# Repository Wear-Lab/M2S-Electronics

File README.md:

# M2S-Electronics
Electronics for the M2S Armband

## Details

This are the EAGLE files used to manufacture the four channel amplifier board
for the M2S Armband.

## JLCPCB manufacturing files

Files used to manufacture the PCB, including Gerber files, BOM, and PnP are
located in the JLCPCB folder.

## 2.5mm TRS Connectors

This board uses 2.5mm Right Angle TRS Connectors, commonly used with audio, 
for receiving analog signals. An example part compatible with this board is the
[SJ1-2503A by Same Sky](https://www.digikey.com/en/products/detail/same-sky-formerly-cui-devices/SJ1-2503A/738680)

## I2C Addresses

This board should have its I2C address set prior to use. To do this, short
one of the jumpers located near the STEMMA QT connectors to select an I2C
Address.

Up to four devices can be hooked up to the same I2C bus.

## I2C Fast Mode

To utilize the full potential of this board, make sure that I2C Fast Mode is
enabled. This ensures that the analog signals are recorded at its designed
maximum speed.

## Electrodes

Electrodes used in the M2S project are based on [DFRobot Gravity Analog EMG
Sensor by OYMotion](https://www.dfrobot.com/product-1661.html).
Eight of these Electrodes are used in the project.

[Wiki page](https://wiki.dfrobot.com/analog_emg_sensor_by_oymotion_sku_sen0240)

## License

This project is licensed under CC BY-NC-SA 4.0. To view a copy of this license,
visit https://creativecommons.org/licenses/by-nc-sa/4.0/

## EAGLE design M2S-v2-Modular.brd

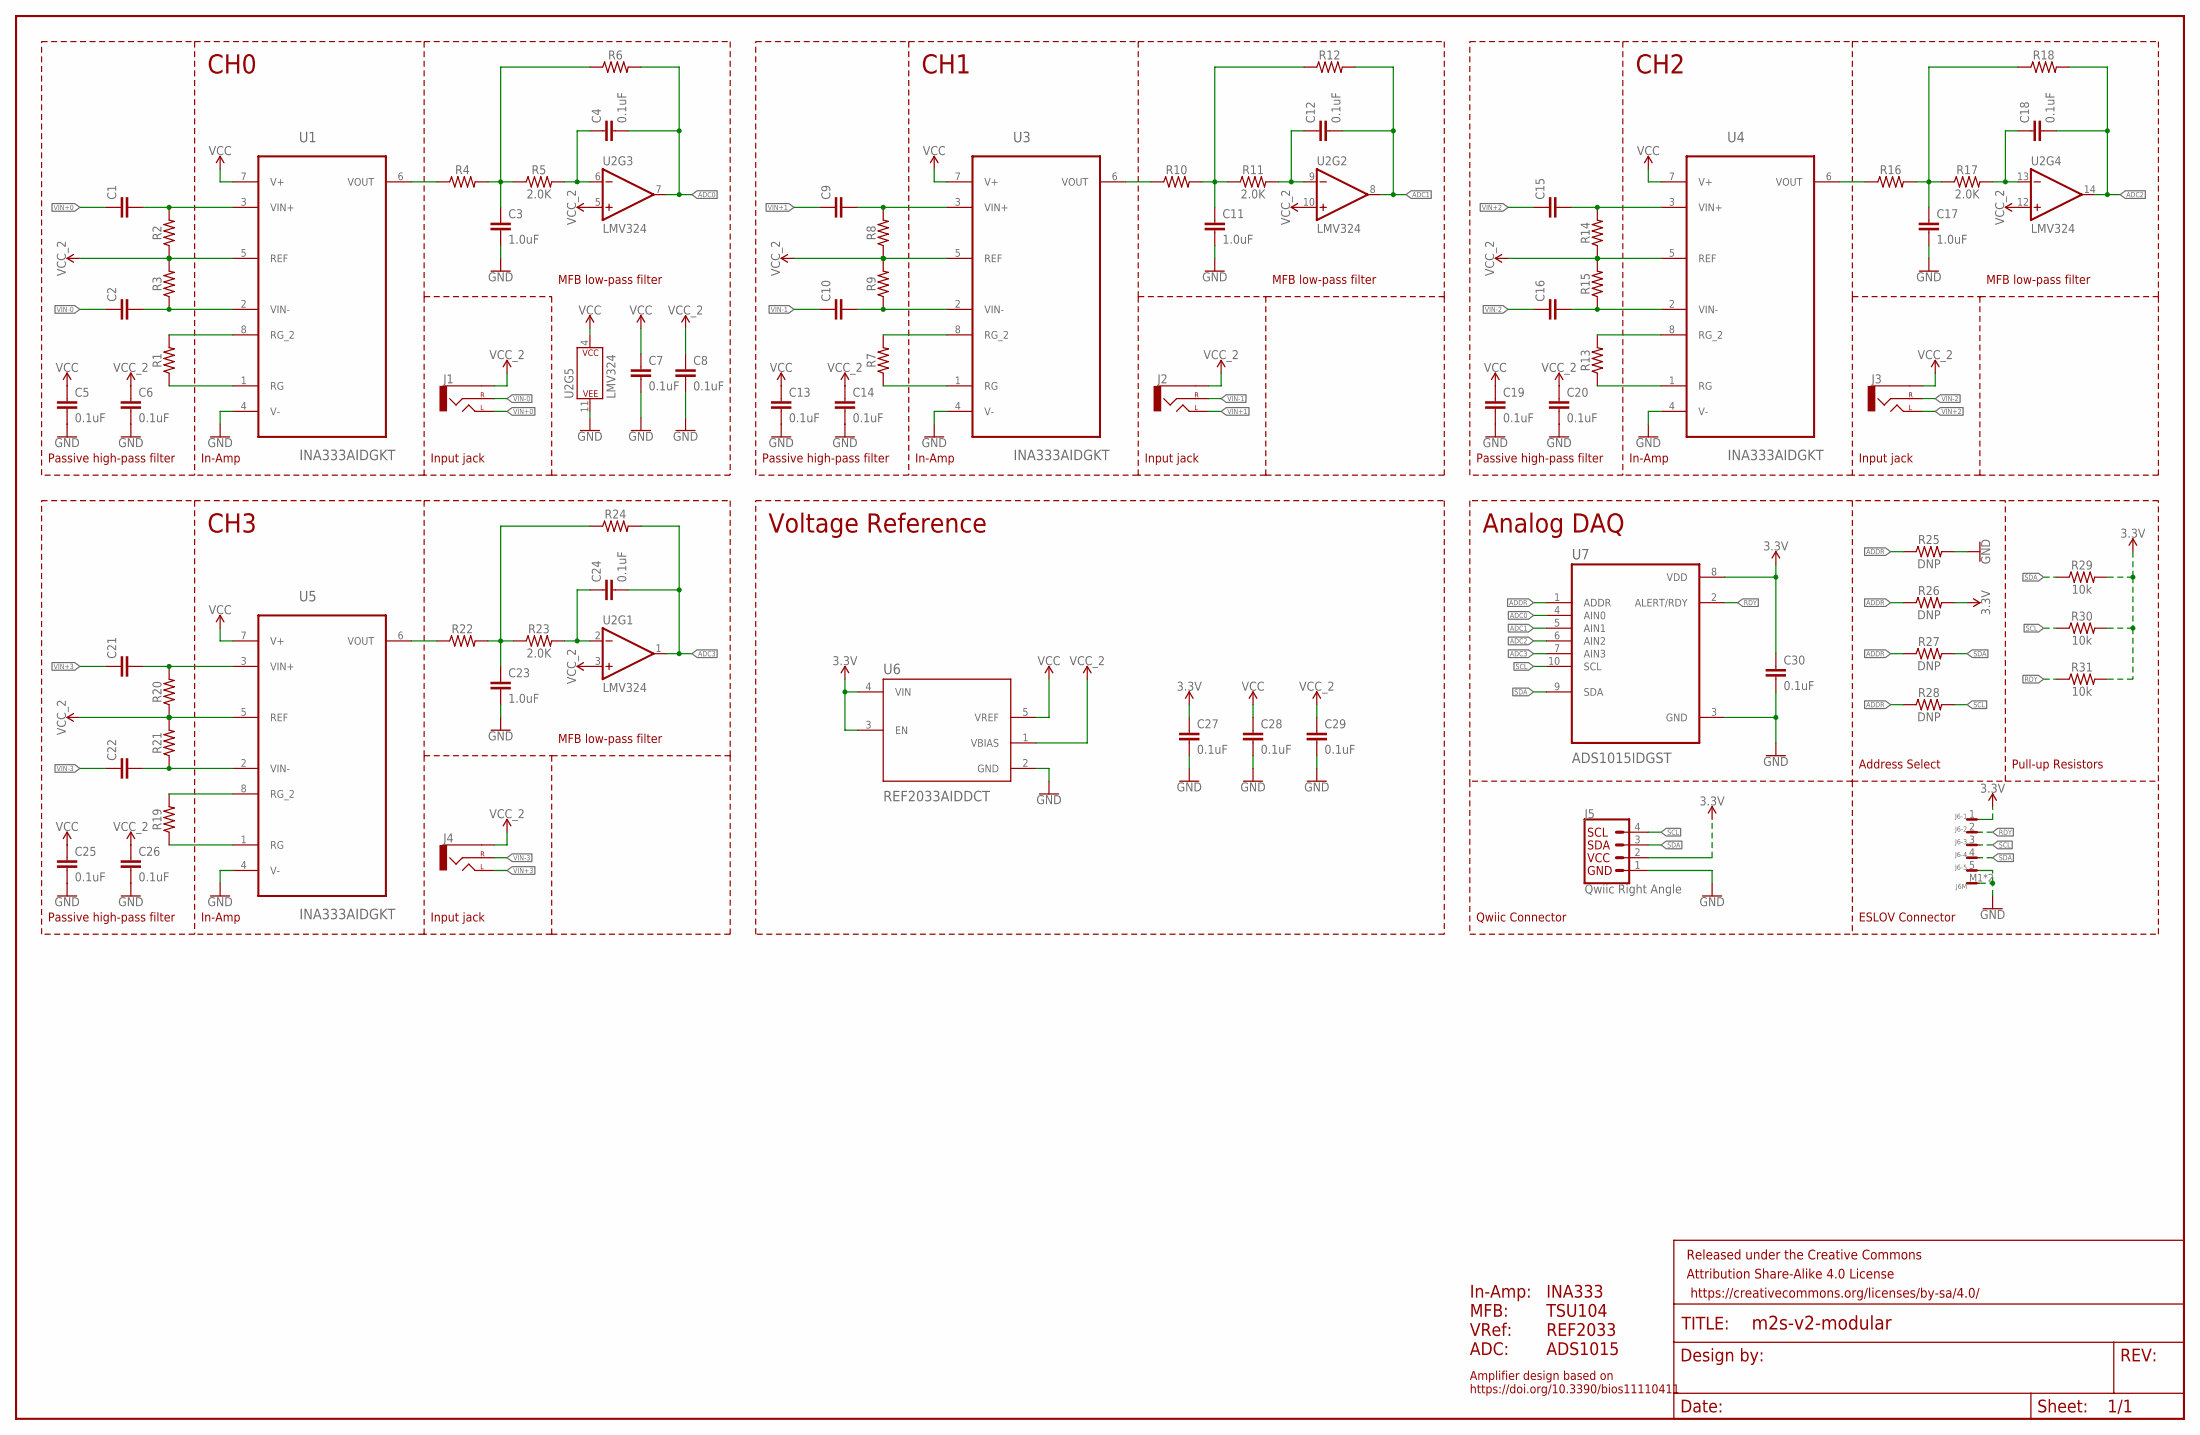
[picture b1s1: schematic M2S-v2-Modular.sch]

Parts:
C1, C2, C9, C10, C15, C16, C21, C22: 0.22uF; 0402
C3, C11, C17, C23: 1.0uF; 0402
C4, C5, C6, C7, C8, C12, C13, C14, C18, C19, C20, C24, C25, C26, C27, C28, C29, C30: 0.1uF; 0402
FRAME1: FRAME-LEDGERNO_FOOTPRINT; DUMMY
J1, J2, J3, J4: AUDIO_JACK_2.5MM_2.5MM; STEREOJACK2.5MM_STEREOJACK2.5MM
J5: Qwiic Right Angle; JST04_1MM_RA
J6: SM05B-SRSS-TB
R1, R7, R13, R19: 1KOHM-0402-1/16W-1%; 0402
R2, R3, R4, R6, R8, R9, R10, R12, R14, R15, R16, R18, R20, R21, R22, R24: 0402
R5, R11, R17, R23: 2.0K; 0402
R25, R26, R27, R28: DNP; 0402
R29, R30, R31: 10k; 0402
U1, U3, U4, U5: INA333AIDGKT; SOP65P490X110-8N
U2: LMV324; SO14
U6: REF2033AIDDCT; SOT95P280X110-5N
U7: ADS1015IDGST; SOP50P490X110-10N

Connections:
3.3V: C27.1, C30.1, J5.2, J6.1, R26.2, R29.2, R30.2, R31.2, U6.3 (EN), U6.4 (VIN), U7.8 (VDD)
ADC0: C4.2, R6.2, U2.7 (OUT), U7.4 (AIN0)
ADC1: C12.2, R12.2, U2.8 (OUT), U7.5 (AIN1)
ADC2: C18.2, R18.2, U2.14 (OUT), U7.6 (AIN2)
ADC3: C24.2, R24.2, U2.1 (OUT), U7.7 (AIN3)
ADDR: R25.1, R26.1, R27.1, R28.1, U7.1 (ADDR)
GND: C3.2, C5.2, C6.2, C7.2, C8.2, C11.2, C13.2, C14.2, C17.2, C19.2, C20.2, C23.2, C25.2, C26.2, C27.2, C28.2, C29.2, C30.2, J5.1, J6.5, J6.M1, J6.M2, R25.2, U1.4 (V-), U2.11 (P$V-), U3.4 (V-), U4.4 (V-), U5.4 (V-), U6.2 (GND), U7.3 (GND)
unnamed: R1.2, U1.8 (RG_2)
unnamed: R1.1, U1.1 (RG)
unnamed: C1.2, R2.2, U1.3 (VIN+)
unnamed: C2.2, R3.1, U1.2 (VIN-)
unnamed: R4.1, U1.6 (VOUT)
unnamed: C3.1, R4.2, R5.1, R6.1
unnamed: C4.1, R5.2, U2.6 (-IN)
unnamed: R7.2, U3.8 (RG_2)
unnamed: R7.1, U3.1 (RG)
unnamed: C9.2, R8.2, U3.3 (VIN+)
unnamed: C10.2, R9.1, U3.2 (VIN-)
unnamed: R10.1, U3.6 (VOUT)
unnamed: C11.1, R10.2, R11.1, R12.1
unnamed: C12.1, R11.2, U2.9 (-IN)
unnamed: R13.2, U4.8 (RG_2)
unnamed: R13.1, U4.1 (RG)
unnamed: C15.2, R14.2, U4.3 (VIN+)
unnamed: C16.2, R15.1, U4.2 (VIN-)
unnamed: R16.1, U4.6 (VOUT)
unnamed: C17.1, R16.2, R17.1, R18.1
unnamed: C18.1, R17.2, U2.13 (-IN)
unnamed: R19.2, U5.8 (RG_2)
unnamed: R19.1, U5.1 (RG)
unnamed: C21.2, R20.2, U5.3 (VIN+)
unnamed: C22.2, R21.1, U5.2 (VIN-)
unnamed: R22.1, U5.6 (VOUT)
unnamed: C23.1, R22.2, R23.1, R24.1
unnamed: C24.1, R23.2, U2.2 (-IN)
RDY: J6.2, R31.1, U7.2 (ALERT/RDY)
SCL: J5.4, J6.3, R28.2, R30.1, U7.10 (SCL)
SDA: J5.3, J6.4, R27.2, R29.1, U7.9 (SDA)
VCC: C5.1, C7.1, C13.1, C19.1, C25.1, C28.1, U1.7 (V+), U2.4 (P$V+), U3.7 (V+), U4.7 (V+), U5.7 (V+), U6.5 (VREF)
VCC_2: C6.1, C8.1, C14.1, C20.1, C26.1, C29.1, J1.RING1 (SLEEVE), J2.RING1 (SLEEVE), J3.RING1 (SLEEVE), J4.RING1 (SLEEVE), R2.1, R3.2, R8.1, R9.2, R14.1, R15.2, R20.1, R21.2, U1.5 (REF), U2.3 (+IN), U2.5 (+IN), U2.10 (+IN), U2.12 (+IN), U3.5 (REF), U4.5 (REF), U5.5 (REF), U6.1 (VBIAS)
VIN+0: C1.1, J1.SHIELD (LEFT)
VIN+1: C9.1, J2.SHIELD (LEFT)
VIN+2: C15.1, J3.SHIELD (LEFT)
VIN+3: C21.1, J4.SHIELD (LEFT)
VIN-0: C2.1, J1.TIP (RIGHT)
VIN-1: C10.1, J2.TIP (RIGHT)
VIN-2: C16.1, J3.TIP (RIGHT)
VIN-3: C22.1, J4.TIP (RIGHT)

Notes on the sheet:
Passive high-pass filter
In-Amp
Input jack
MFB low-pass filter
CH0
In-Amp: MFB: VRef: ADC:
INA333 TSU104 REF2033 ADS1015
Amplifier design based on https://doi.org/10.3390/bios11110411
CH1
CH2
CH3
Voltage Reference
Analog DAQ
Address Select
Qwiic Connector
ESLOV Connector
Pull-up Resistors

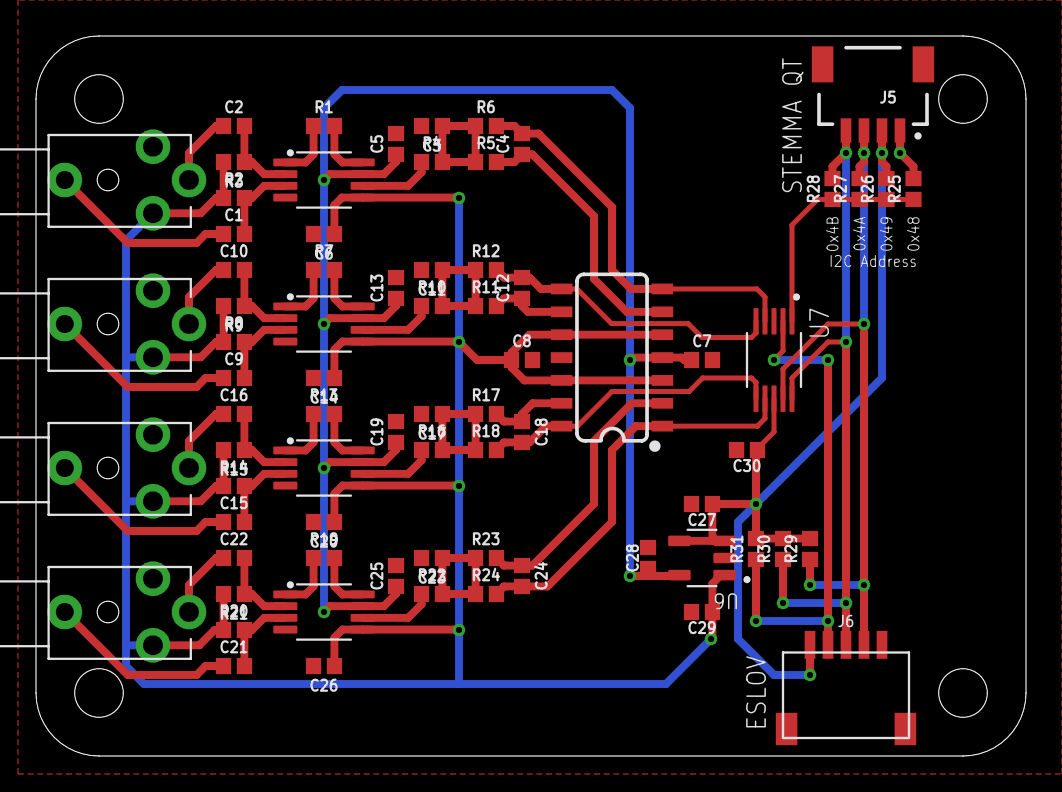
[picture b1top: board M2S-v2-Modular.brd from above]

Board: 2 copper layers, 55.0 x 40.0 mm, 75 parts (0 on the bottom side), 48 nets.

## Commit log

2025-10-21 ADC Fix
    Changed ADC from ADS1115 to ADS1015.
    Added EAGLE libraries.
    Updated/Fixed JLCPCB BOM and PnP files.
    Added PDF for the schematics for easier access.
2025-10-30 Fix ESLOV Pinout
    Fixed ESLOV Pinout, swapped SDA and INT pins.

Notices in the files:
parts and their libraries:
SparkFun-Capacitors: Licensing: Creative Commons ShareAlike 4.0 International - https://creativecommons.org/licenses/by-sa/4.0
SparkFun-Aesthetics: Released under the Creative Commons Attribution Share-Alike 4.0 License
SparkFun-Aesthetics: https://creativecommons.org/licenses/by-sa/4.0
